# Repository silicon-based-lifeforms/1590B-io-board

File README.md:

# 1590B-io-board 

An open-hardware PCB designed for making guitar pedals using Hammond 1590B enclosures.

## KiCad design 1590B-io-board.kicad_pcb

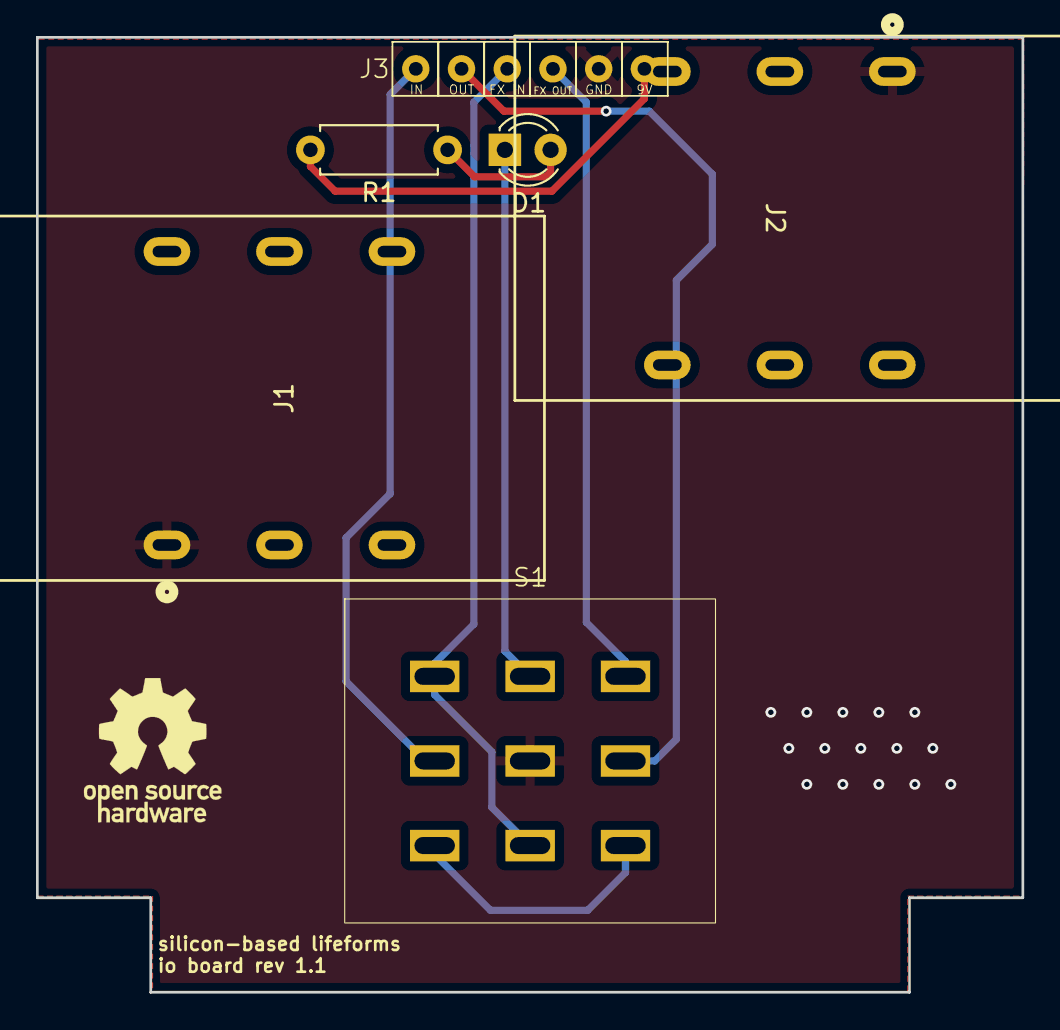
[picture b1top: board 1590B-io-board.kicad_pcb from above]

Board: 2 copper layers, 54.8 x 53.1 mm, 6 parts (0 on the bottom side), 9 nets.

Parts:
D1: LED; LED_D3.0mm
J1, J2: ACJS-MHOM; Amphenol_ACJS-IH
J3: Conn_01x04; 01x06_2.54mm_Ribbon_Pads
R1: R; R_Axial_DIN0207_L6.3mm_D2.5mm_P7.62mm_Horizontal
S1: 3PDT; Tayda_3PDT_A-1844

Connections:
/9V: J3.6, R1.2
/FX_INPUT: J3.3, S1.1, S1.6
/FX_OUTPUT: J3.4, S1.7
/INPUT_JACK_TIP: J1.T, J3.1, S1.2
/OUTPUT_JACK_TIP: J2.T, J3.2, S1.8
GND: J1.S, J2.S, J3.5, S1.5
unnamed: D1.2 (A), R1.1
unnamed: D1.1 (K), S1.4
unnamed: S1.3, S1.9

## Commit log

2024-04-26 Inital commit of rev 1 PCB
2024-04-29 Add a few misc. adjustments
2024-04-29 Add rendering of PCB
2024-05-08 Add 01x03 and 01x06 ribbon cable pads
2024-05-08 Update board dimensions and jack layout
